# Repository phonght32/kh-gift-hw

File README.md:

# kh-gift-hw

### 1. Overview

### 2. Specifications

| Items            | Specifications                                    |
| ---------------- | ------------------------------------------------- |
| Power supply     | Pin LiPo 1 cell                                   |
| Microcontroller  | ESP32                                             |
| LEDs and Buttons | LED Charge<br />LED Standby<br />User push button |
| Dimensions       | 89.4 x55 mm<br />Screw hole 83.4 x 49 mm          |

### 3. Hardware design

#### Schematic

#### PCB Top

#### PCB Bot

#### Dimension

#### 3D Top

#### 3D Bot

### 4. Bill of Materials (BOM)

[Download v2.0](assets/BOM/BOM_kh-gift-hw_v2.0.xlsx)

### 5. Gerber

[Download v1.0](assets/Gerber/Gerber_kh-gift-hw_v1.0.zip)

[Download v2.0](assets/Gerber/Gerber_kh-gift-hw_v2.0.zip)

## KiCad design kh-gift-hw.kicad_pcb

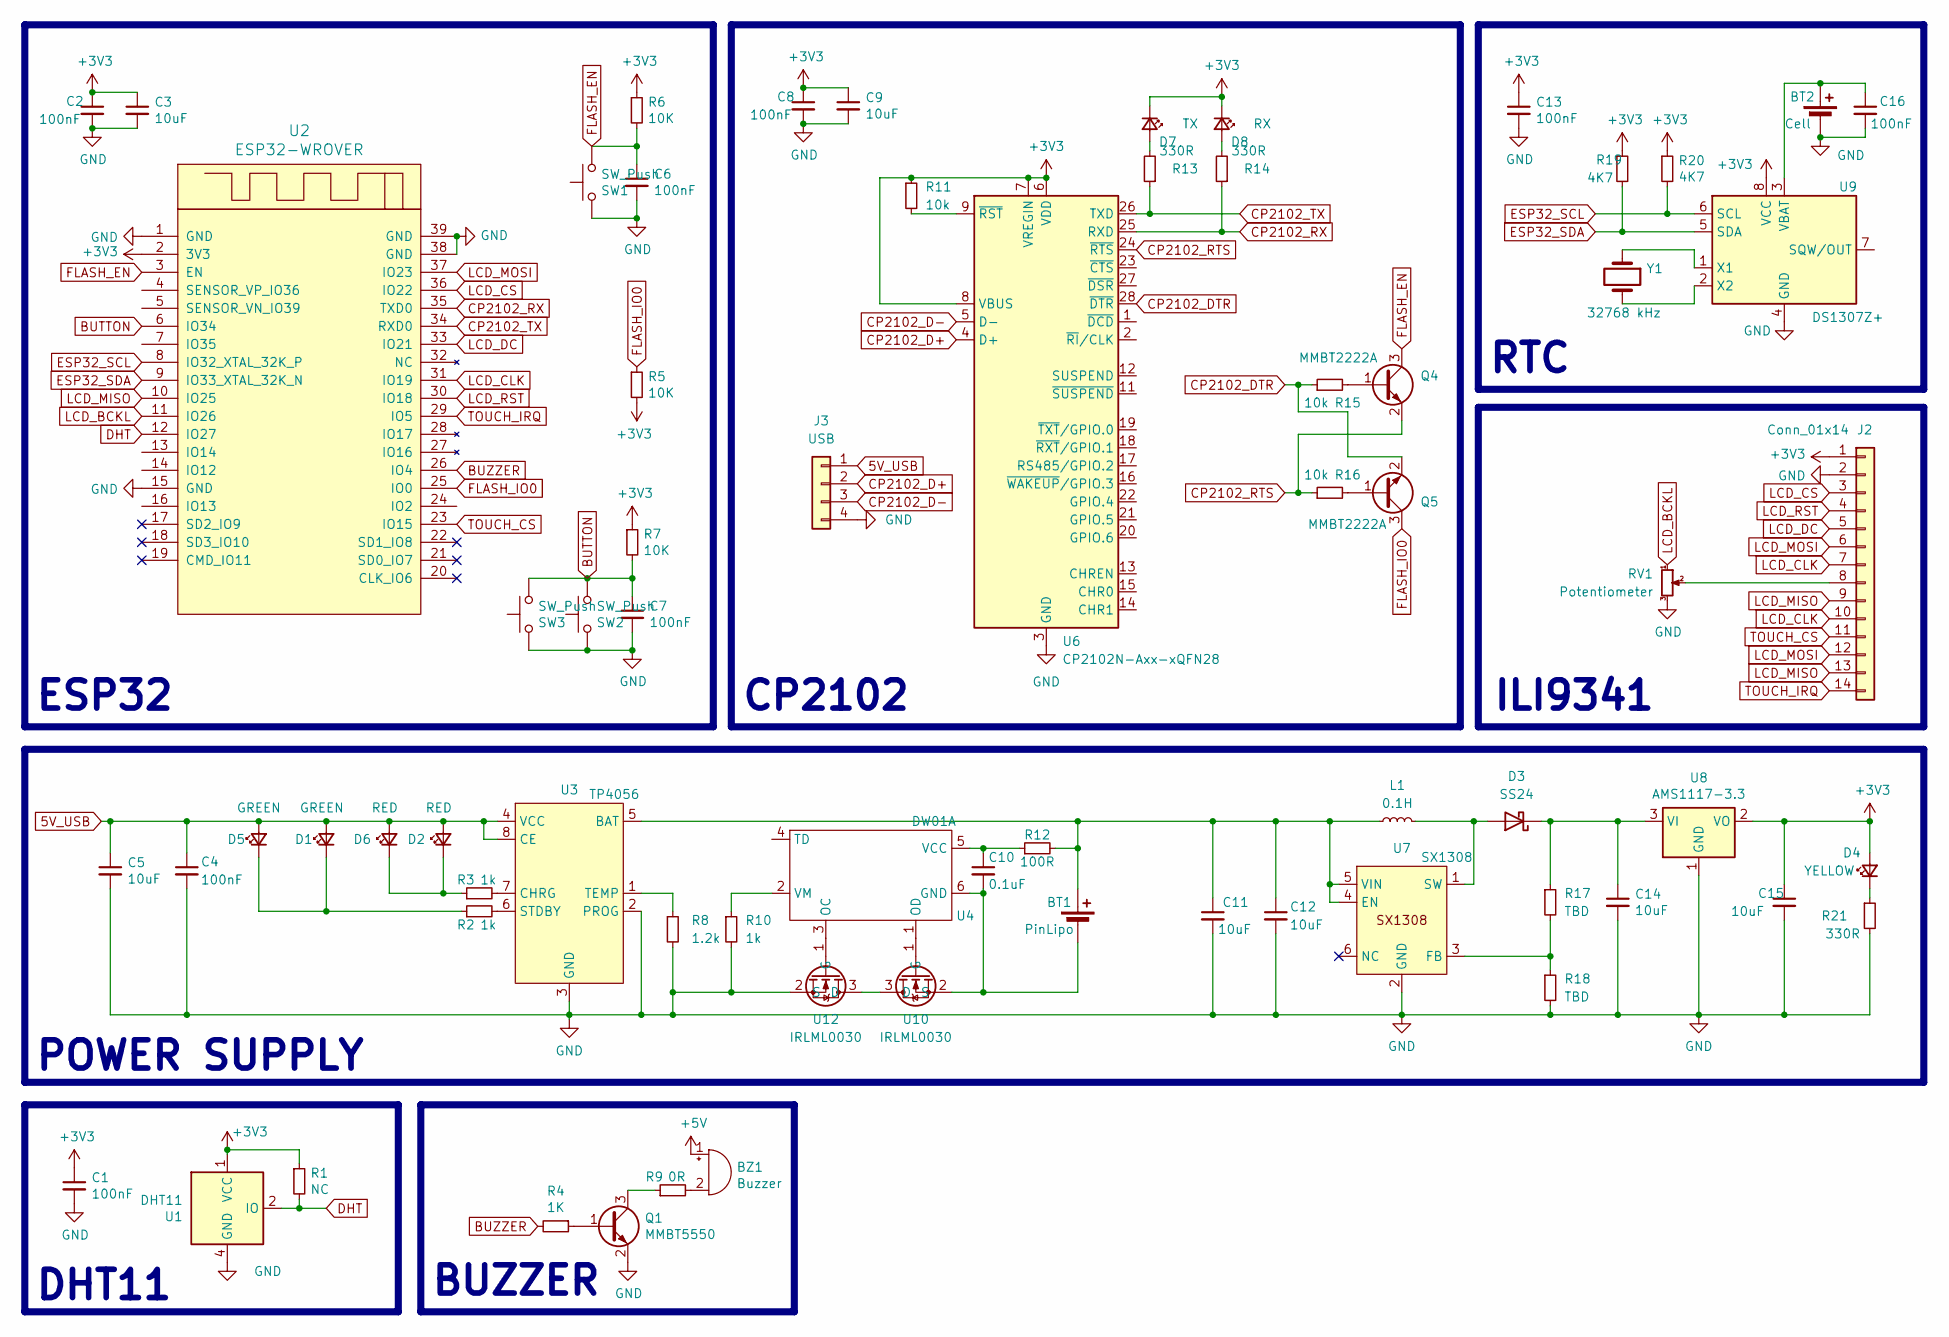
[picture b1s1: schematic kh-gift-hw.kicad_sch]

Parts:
BT1: PinLipo; JST_EH_S2B-EH_1x02_P2.5mm_Horizontal
BT2: Cell; BAT_CR1220_Holder
BZ1: Buzzer; MagneticBuzzer_Kobitone_254-EMB84Q-RO
C1, C2: 100nF; C_1210_3225Metric
C3, C5, C11, C12, C14, C15: 10uF; C_1210_3225Metric
C4, C6, C7, C8, C13, C16: 100nF; C_0603_1608Metric
C9: 10uF; C_0603_1608Metric
C10: 0.1uF; C_1210_3225Metric
D1: GREEN; LED_0603_1608Metric_Pad1.05x0.95mm_HandSolder
D2: RED; LED_0603_1608Metric_Pad1.05x0.95mm_HandSolder
D3: SS24; D_SMA
D4: YELLOW; LED_0603_1608Metric_Pad1.05x0.95mm_HandSolder
D5: GREEN; Connector_ZH_1x02_P1.25mm_Horizontal
D6: RED; Connector_ZH_1x02_P1.25mm_Horizontal
D7: TX; LED_0603_1608Metric_Pad1.05x0.95mm_HandSolder
D8: RX; LED_0603_1608Metric_Pad1.05x0.95mm_HandSolder
J2: Conn_01x14; ili9341_3.2inch
J3: USB; JST_EH_S4B-EH_1x04_P2.5mm_Horizontal
L1: 0.1H; L_Coilcraft_XAL5030-XXX
Q1: MMBT5550; SOT-23
Q4, Q5: MMBT2222A; SOT-23
R1: NC; R_0603_1608Metric
R2, R3, R10: 1k; R_0603_1608Metric
R4: 1K; R_0603_1608Metric
R5, R6, R7: 10K; R_0603_1608Metric
R8: 1.2k; R_0603_1608Metric
R9: 0R; R_0603_1608Metric
R11, R15, R16: 10k; R_0603_1608Metric
R12: 100R; R_0603_1608Metric
R13, R14, R21: 330R; R_0603_1608Metric
R17, R18: TBD; R_0603_1608Metric
R19, R20: 4K7; R_0603_1608Metric
RV1: Potentiometer; Connector_ZH_1x03_P1.25mm_Horizontal
SW1, SW2: SW_Push; PushButton_6x6mm_SMD
SW3: SW_Push; Connector_ZH_1x02_P1.25mm_Horizontal
U1: DHT11; SNR4-2.54-15.5X12.0X5.5MM
U2: ESP32-WROVER
U3: TP4056; SOP127P600X175-9N
U4: DW01A; TSOT-23-6
U6: CP2102N-Axx-xQFN28; QFN-28-1EP_5x5mm_P0.5mm_EP3.35x3.35mm
U7: SX1308; TSOT-23-6
U8: AMS1117-3.3; SOT-223-3_TabPin2
U9: DS1307Z+; SOIC-8_3.9x4.9mm_P1.27mm
U10, U12: IRLML0030; SOT-23
Y1: 32768 kHz; Crystal_SMD_3215-2Pin_3.2x1.5mm

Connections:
5V_USB: C4.1, C5.1, D1.2 (A), D2.2 (A), D5.2 (A), D6.2 (A), J3.1, U3.4 (VCC), U3.8 (CE)
+3V3: C1.1, C2.1, C3.1, C8.1, C9.1, C13.1, C15.1, D4.2 (A), D7.1 (K), D8.1 (K), J2.1, R1.1, R5.2, R6.1, R7.1, R11.1, R19.1, R20.1, U1.1 (VCC), U2.2 (3V3), U6.6 (VDD), U6.7 (VREGIN), U6.8 (VBUS), U8.2 (VO), U9.8 (VCC)
+5V: BZ1.1 (-)
BUTTON: C7.1, R7.2, SW2.1, SW3.1, U2.6 (IO34)
BUZZER: R4.2, U2.26 (IO4)
CP2102_D+: J3.2, U6.4 (D+)
CP2102_D-: J3.3, U6.5 (D-)
CP2102_DTR: Q5.2 (E), R15.1, U6.28 (~DTR)
CP2102_RTS: Q4.2 (E), R16.1, U6.24 (~RTS)
CP2102_RX: R14.1, U2.35 (TXD0), U6.25 (RXD)
CP2102_TX: R13.1, U2.34 (RXD0), U6.26 (TXD)
DHT: R1.2, U1.2 (IO), U2.12 (IO27)
ESP32_SCL: R20.2, U2.8 (IO32_XTAL_32K_P), U9.6 (SCL)
ESP32_SDA: R19.2, U2.9 (IO33_XTAL_32K_N), U9.5 (SDA)
FLASH_EN: C6.1, Q4.3 (C), R6.2, SW1.1, U2.3 (EN)
FLASH_IO0: Q5.3 (C), R5.1, U2.25 (IO0)
GND: BT2.2 (-), C1.2, C2.2, C3.2, C4.2, C5.2, C6.2, C7.2, C8.2, C9.2, C11.2, C12.2, C13.2, C14.2, C15.2, C16.2, J2.2, J3.4, Q1.2 (E), R8.2, R10.2, R18.2, R21.2, RV1.3, SW1.2, SW2.2, SW3.2, U1.4 (GND), U2.1 (GND), U2.15 (GND), U2.38 (GND), U2.39 (GND), U3.2 (PROG), U3.3 (GND), U6.3 (GND), U6.29 (GND), U7.2 (GND), U8.1 (GND), U9.4 (GND), U12.2 (S)
LCD_BCKL: RV1.1, U2.11 (IO26)
LCD_CLK: J2.7, J2.10, U2.31 (IO19)
LCD_CS: J2.3, U2.36 (IO22)
LCD_DC: J2.5, U2.33 (IO21)
LCD_MISO: J2.9, J2.13, U2.10 (IO25)
LCD_MOSI: J2.6, J2.12, U2.37 (IO23)
LCD_RST: J2.4, U2.30 (IO18)
unnamed: BT1.1 (+), C11.1, C12.1, L1.1, R12.2, U3.5 (BAT), U7.4 (EN), U7.5 (VIN)
unnamed: BT1.2 (-), C10.2, U4.6 (GND), U10.2 (S)
unnamed: BT2.1 (+), C16.1, U9.3 (VBAT)
unnamed: BZ1.2 (+), R9.2
unnamed: D1.1 (K), D5.1 (K), R2.1
unnamed: D2.1 (K), D6.1 (K), R3.1
unnamed: D3.2 (A), L1.2, U7.1 (SW)
unnamed: C14.1, D3.1 (K), R17.1, U8.3 (VI)
unnamed: D4.1 (K), R21.1
unnamed: D7.2 (A), R13.2
unnamed: D8.2 (A), R14.2
unnamed: J2.8, RV1.2
unnamed: Q1.1 (B), R4.1
unnamed: Q1.3 (C), R9.1
unnamed: Q4.1 (B), R15.2
unnamed: Q5.1 (B), R16.2
unnamed: R3.2, U3.7 (CHRG)
unnamed: R2.2, U3.6 (STDBY)
unnamed: R8.1, U3.1 (TEMP)
unnamed: C10.1, R12.1, U4.5 (VCC)
unnamed: R10.1, U4.2 (VM)
unnamed: R11.2, U6.9 (~RST)
unnamed: R17.2, R18.1, U7.3 (FB)
unnamed: U9.1 (X1), Y1.1
unnamed: U9.2 (X2), Y1.2
unnamed: U10.3 (D), U12.3 (D)
unnamed: U4.1 (OD), U10.1 (G)
unnamed: U4.3 (OC), U12.1 (G)
TOUCH_CS: J2.11, U2.23 (IO15)
TOUCH_IRQ: J2.14, U2.29 (IO5)

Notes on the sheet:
ESP32
RTC
POWER SUPPLY
DHT11
ILI9341
BUZZER
CP2102

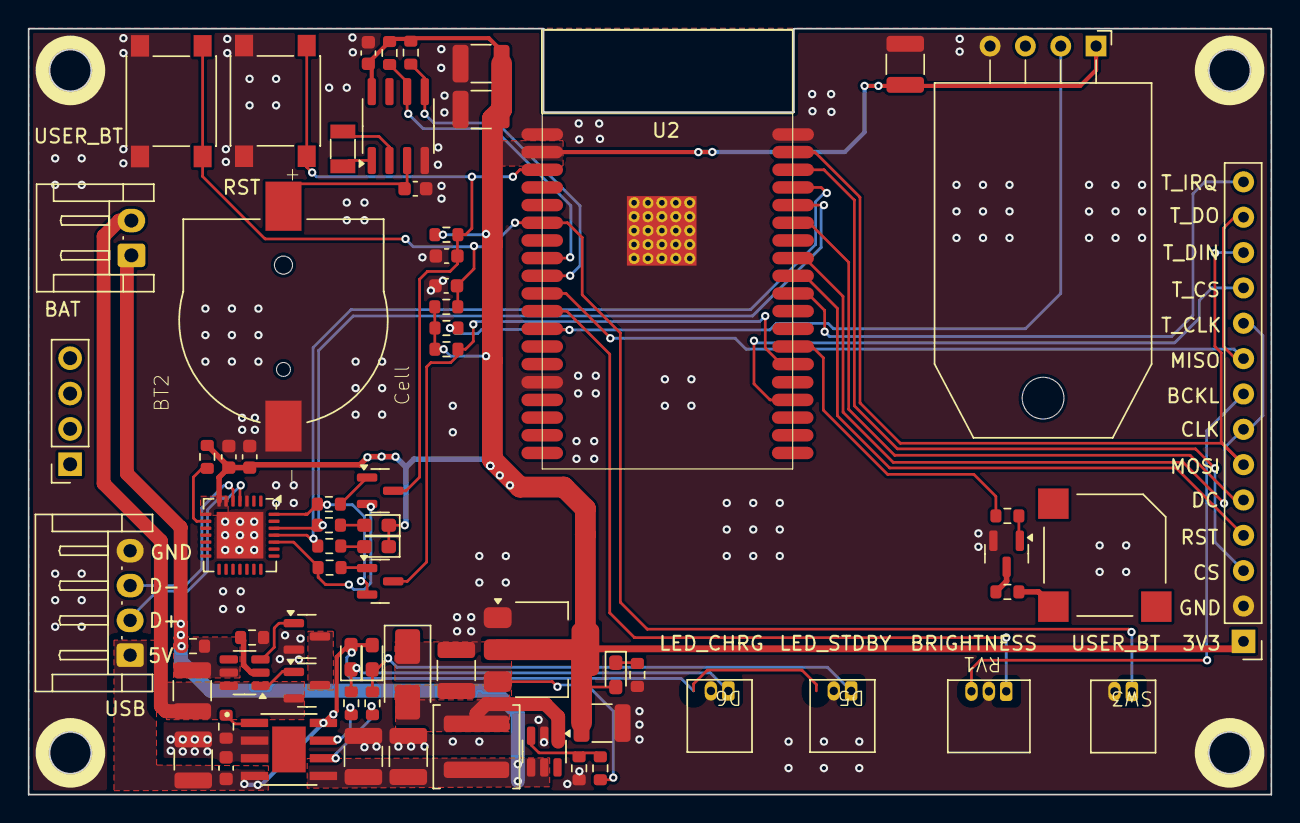
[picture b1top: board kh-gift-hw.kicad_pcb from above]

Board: 2 copper layers, 89.3 x 55.0 mm, 69 parts (0 on the bottom side), 53 nets.

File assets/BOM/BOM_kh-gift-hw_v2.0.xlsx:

Reference | Value | Footprint | Qty
BT1 | PinLipo | footprints:JST_EH_S2B-EH_1x02_P2.5mm_Horizontal | 1
BT2 | Cell | footprints:BAT_CR1220_Holder | 1
BZ1 | Buzzer | Buzzer_Beeper:MagneticBuzzer_Kobitone_254-EMB84Q-RO | 1
C1,C2 | 100nF | Capacitor_SMD:C_1210_3225Metric | 2
C3,C5,C11,C12,C14,C15 | 10uF | Capacitor_SMD:C_1210_3225Metric | 6
C4,C6,C7,C8,C13,C16 | 100nF | Capacitor_SMD:C_0603_1608Metric | 6
C9 | 10uF | Capacitor_SMD:C_0603_1608Metric | 1
C10 | 0.1uF | Capacitor_SMD:C_1210_3225Metric | 1
D1 | GREEN | LED_SMD:LED_0603_1608Metric_Pad1.05x0.95mm_HandSolder | 1
D2 | RED | LED_SMD:LED_0603_1608Metric_Pad1.05x0.95mm_HandSolder | 1
D3 | SS24 | Diode_SMD:D_SMA | 1
D4 | YELLOW | LED_SMD:LED_0603_1608Metric_Pad1.05x0.95mm_HandSolder | 1
D5 | GREEN | footprints:JST_EH_S2B-EH_1x02_P2.5mm_Horizontal | 1
D6 | RED | footprints:JST_EH_S2B-EH_1x02_P2.5mm_Horizontal | 1
D7 | TX | LED_SMD:LED_0603_1608Metric_Pad1.05x0.95mm_HandSolder | 1
D8 | RX | LED_SMD:LED_0603_1608Metric_Pad1.05x0.95mm_HandSolder | 1
J2 | Conn_01x14 | footprints:ili9341_3.2inch | 1
J3 | USB | footprints:JST_EH_S4B-EH_1x04_P2.5mm_Horizontal | 1
L1 | 0.1H | Inductor_SMD:L_Coilcraft_XAL5030-XXX | 1
Q1 | MMBT5550 | Package_TO_SOT_SMD:SOT-23 | 1
Q4,Q5 | MMBT2222A | Package_TO_SOT_SMD:SOT-23 | 2
R1 | NC | Resistor_SMD:R_0603_1608Metric | 1
R2,R3,R10 | 1k | Resistor_SMD:R_0603_1608Metric | 3
R4 | 1K | Resistor_SMD:R_0603_1608Metric | 1
R5,R6,R7 | 10K | Resistor_SMD:R_0603_1608Metric | 3
R8 | 1.2k | Resistor_SMD:R_0603_1608Metric | 1
R9 | 0R | Resistor_SMD:R_0603_1608Metric | 1
R11,R15,R16 | 10k | Resistor_SMD:R_0603_1608Metric | 3
R12 | 100R | Resistor_SMD:R_0603_1608Metric | 1
R13,R14,R21 | 330R | Resistor_SMD:R_0603_1608Metric | 3
R17,R18 | TBD | Resistor_SMD:R_0603_1608Metric | 2
R19,R20 | 4K7 | Resistor_SMD:R_0603_1608Metric | 2
RV1 | Potentiometer | footprints:JST_EH_S3B-EH_1x03_P2.5mm_Horizontal | 1
SW1,SW2 | SW_Push | footprints:PushButton_6x6mm_SMD | 2
SW3 | SW_Push | footprints:JST_EH_S2B-EH_1x02_P2.5mm_Horizontal | 1
U1 | DHT11 | footprints:SNR4-2.54-15.5X12.0X5.5MM | 1
U2 | ESP32-WROVER | footprints:ESP32-WROVER | 1
U3 | TP4056 | footprints:SOP127P600X175-9N | 1
U4 | DW01A | Package_TO_SOT_SMD:TSOT-23-6 | 1
U6 | CP2102N-Axx-xQFN28 | Package_DFN_QFN:QFN-28-1EP_5x5mm_P0.5mm_EP3.35x3.35mm | 1
U7 | SX1308 | Package_TO_SOT_SMD:TSOT-23-6 | 1
U8 | AMS1117-3.3 | Package_TO_SOT_SMD:SOT-223-3_TabPin2 | 1
U9 | DS1307Z+ | Package_SO:SOIC-8_3.9x4.9mm_P1.27mm | 1
U10,U12 | IRLML0030 | Package_TO_SOT_SMD:SOT-23 | 2
Y1 | 32768 kHz | footprints:Crystal_SMD_3215-2Pin_3.2x1.5mm | 1

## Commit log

2021-01-29 add basic
2021-01-31 update library
2021-01-31 complete project
2024-01-06 remove kicad-library
2024-01-14 update routing
2024-02-07 add crystal
2024-02-07 remove backup
2024-02-07 update board shape
2024-02-07 update pcb
2024-02-07 update gitignore
2024-02-07 update demo
2024-02-07 remove backup file
2024-02-07 remove pin 1 notify
2024-02-07 add USB pinout description
2024-03-02 update gerber
2024-03-02 update project setting for Kicad v8
2024-03-02 add BOM
2024-03-02 update project
2024-07-11 remove gerber folder
2024-07-11 update BOM
2025-09-22 update footprint
2025-12-14 update libarary
